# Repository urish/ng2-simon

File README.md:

# ng2-simon

A Universal Simon game written in Angular 2.

It runs on the web browser, on Arduino and also on the Raspberry PI using [angular2-iot](https://github.com/urish/angular2-iot).

➡ [Learn how to works and how you can build your own version](https://medium.com/@urish/building-simon-with-angular2-iot-fceb78bb18e5)

## Live Demo (browser)

[Go to the online version](https://urish.github.io/ng2-simon/)

## Running in a Web Browser

    npm install
    npm start

Then go to [http://localhost:3000](http://localhost:3000) in your browser.

## Running on Raspberry Pi

### Hardware Assembly

1. Connect 4 push-buttons, one button between each of pins GPIO-13, GPIO-26, GPIO-16, GPIO-21 and the ground
2. Connect 4 colored LEDs, one LED between each of pins GPIO-6, GPIO-19, GPIO-12, GPIO-20 and the ground. It is also recommended to add a 100ohm current limiting resistor in series with each LED.
3. Connect a speaker to the Raspberry PI audio jack
4. Optionally, connect a [Serial 7-Segment Display](https://www.sparkfun.com/products/11442) to the I2C pins of the Raspberry Pi: connect GPIO-2 to SDL and GPIO-3 to SCL

### Running the game

Run the following command on the Raspberry pi terminal / console:

1. Make sure you have the `sox` and `mpg123` packages installed: `sudo apt-get install sox mpg123`
2. Build the project using `npm run build:iot`
3. Run it using `sudo npm run iot`

## Running on Arduino

### Hardware Assembly

1. Connect 4 push-buttons, one button between each of Arduino pins 2, 3, 4, 5 and the ground
2. Connect 4 colored LEDs, one LED between each of Arduino pins 9, 10, 11, 12 and a current limiting resistor connected to the ground. 220ohm is a good value for the resistor.
3. Optionally, connect a small speaker between pin 8 and the ground

### Running the game

1. Connect the Arduino board to your computer
2. Upload the [StandardFirmata firmware](https://github.com/firmata/arduino) firmware to your Arduino board
3. Build the project using `npm run build:iot`
4. Run it using `npm run iot`

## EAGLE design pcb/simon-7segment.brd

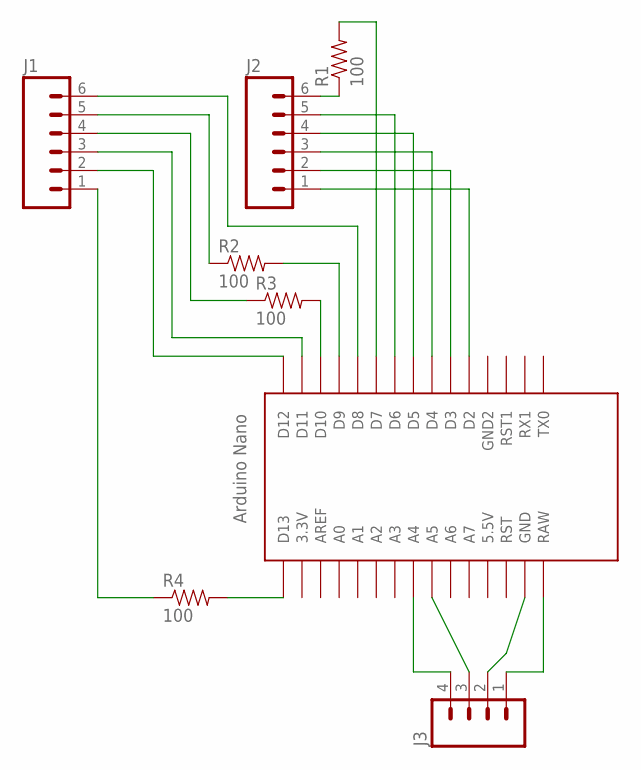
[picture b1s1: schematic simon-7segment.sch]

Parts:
J1, J2: M06SILK_FEMALE_PTH; 1X06
J3: M04LOCK_LONGPADS; 1X04_LOCK_LONGPADS
R1, R2, R3, R4: 100; AXIAL-0.4
U$1: NANO

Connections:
5V: J3.1, U$1.RAW
12: J1.1, R4.P$1 (1)
GND: J3.2, U$1.GND
unnamed: J2.1, U$1.D2
unnamed: J2.2, U$1.D3
unnamed: J2.3, U$1.D4
unnamed: J2.4, U$1.D5
unnamed: J2.5, U$1.D6
unnamed: J2.6, R1.P$1 (1)
unnamed: R1.P$2 (2), U$1.D7
unnamed: J1.6, U$1.D8
unnamed: J1.5, R2.P$1 (1)
unnamed: R2.P$2 (2), U$1.D9
unnamed: J1.4, R3.P$1 (1)
unnamed: R3.P$2 (2), U$1.D10
unnamed: J1.3, U$1.D11
unnamed: J1.2, U$1.D12
unnamed: R4.P$2 (2), U$1.D13
SCL: J3.3, U$1.A5
SDA: J3.4, U$1.A4

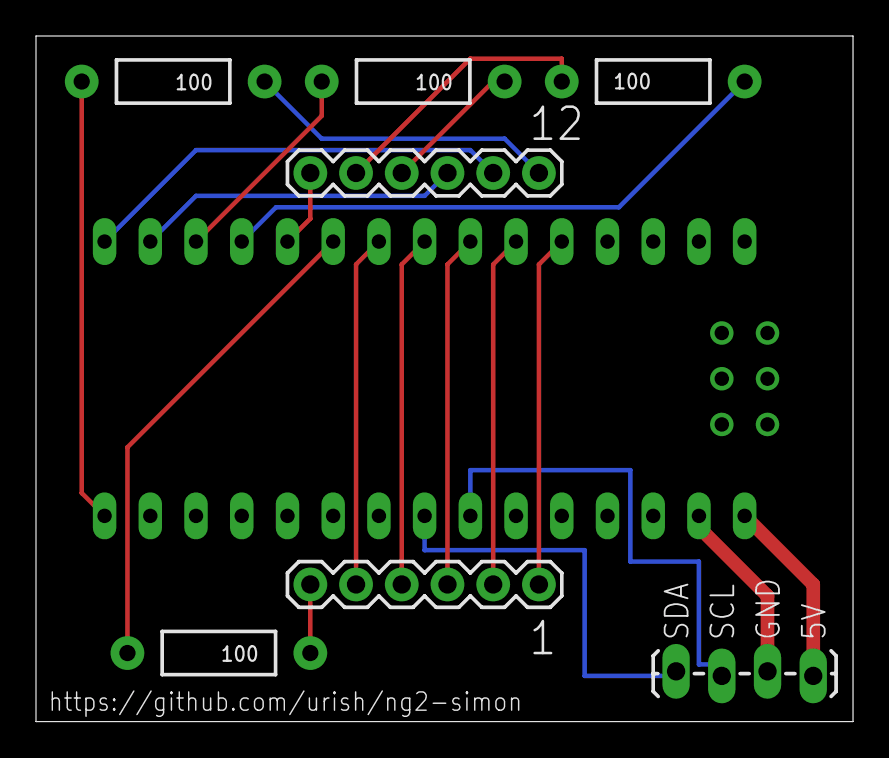
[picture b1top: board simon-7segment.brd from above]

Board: 2 copper layers, 45.4 x 38.1 mm, 8 parts (0 on the bottom side), 20 nets.

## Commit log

2016-04-18 add basic game logic
2016-04-18 chore(*): fix tslint.json
2016-04-19 feat(iot): add an entry point for IoT
2016-04-19 fix(*): fix build configration for the web version
2016-04-19 feat(game): add sound (using 8 bit audio API)
2016-04-19 fix(iot): import correct package name
2016-04-19 fix(iot): handle the case where WebAudio is not available (such as on IoT platform)
2016-04-19 feat(iot): implement AnalogSynth and SevenSegment components
2016-04-19 doc(README): update readme
2016-04-19 fix(iot): remove a debug print
2016-04-19 doc(README): add instructions for running in the browser
2016-04-19 doc(README): fix instructions
2016-04-28 doc(README): add a diagram for Arduino + instructions
2016-04-28 feat(SevenSegment): switch from cli i2c to raspi-io based i2c
2016-04-28 doc(README): update raspi instructions
2016-04-29 feat(simon): add a game over sound file
2016-04-29 feat(simon): css facelift
2016-04-29 feat(simon): deploy to gh-pages
2016-04-29 doc(README): add link to the live demo
2016-04-29 feat(simon): more pleasant level-up sound
2016-04-29 feat(simon): add a "star on github" widget
2016-04-30 fix(iot): disable johnny-five REPL
2016-05-01 fix(simon): normalize audio levels
2016-05-01 chore(*): upgrade npm deps
2016-05-01 doc(*): update project name in package.json
2016-05-01 fix(*): add raspi-io and phantomjs to optionalDependecies
    this lets us run the code on the raspberry pi
2016-05-01 feat(simon): add mp3 playing support for raspberry pi
2016-05-01 doc(README): fix a typo
2016-05-01 doc(readme): explain raspberry pi hardware setup + diagram
2016-05-01 doc(raspi): add a sample alsa config for raspberry pi
2016-05-01 feat(simon): use common base class for IoT and Web audio synth
    thanks @pascalprecht for helping out
2016-05-02 feat(simon): add raspberry pi code
    iot directives + pin mappings + seven segment display
2016-05-02 feat(simon): wait for the player before starting the game
2016-05-03 feat(iot): use raspiberry pi IO by default
2016-05-03 feat(simon): report game state and game score to firebase
2016-05-04 linear tone duration (300 -> 100)
2016-05-04 new high score sound added
2016-10-13 Initial commit (clone angular2-webpack-starter)
2016-10-13 Merge pull request #1 from tomteman/master
    linear tone duration (300 -> 100)
2016-10-13 Merge pull request #2 from tomteman/master
    new high score sound added
2016-10-13 feat(simon): keep track of the game color
    and also add some documentation
2016-10-13 core(material-design): remove extra MD dependencies
2016-10-13 refactor(simon): move to firebase bits into a service
2016-10-13 feat(simon): Use a different Firebase URL for web / iot
    fix #4
2016-10-13 feat(simon): store last button color to firebase
2016-10-13 feat(simon): add optional firebase auth
2016-10-13 feat(simon): report the current sequence index to Firebase
2016-10-13 chore(*): angular 2.0.0-rc.1
2016-10-13 add a PCB design for I2C 7Segment adapter
2016-10-13 feat(simon): indicate game over to firebase
2016-10-13 USB Audio configuration
    + explanations for asound.conf
2016-10-13 add enclouse design files (laser cut)
2016-10-13 chore(*): upgrade typings to 1.0
2016-10-13 fix(iot): add missing dependencies
    @angular/http and @angular/router-deprecated are required by angular-universal
2016-10-13 rename iot.ts -> main.iot.ts
2016-10-13 fix(iot): fix broken iot bootstrap
    Apparently, `bootstrap()` fails if the component has a `selector` property. Thus, we create an intermediate `SimonIotApp` component to bootstrap the game.
2016-10-13 add 3d model of the dowels
2016-10-13 doc(README): add a link to the blog post
2016-10-13 fix(iot): handle i2c errors gracefully
2016-10-13 Update raspberry pi pin mapping
    Apparently, some of the pins we previous used are shared with the PCM driver, thus blocking the built-in sound card from being used.
2016-10-13 refactor(*): angular 2.0 final
    also migrate to angular-cli and typescript 2
2016-10-13 cleanup(*): remove last portions of angular2-webpack-starter code
2016-10-13 refactor(*): renames files following Angular 2 style guide conventions
2016-10-15 fix(iot): add angular iot dependencies
    also fix the IoT bootstrap code
2016-10-22 feat(build): enable AoT for Web build
    also upgrade angular to 2.1
2016-10-22 fix(build): add gh-pages to pacakge.json
2016-10-22 fix(game): remove `private` from view props
    remove the `private` qualifier from properties shared with the view (for AoT)
2016-10-22 fix(iot): fix iot module configuration
2016-10-22 fix(iot): update npm dependencies
    angular 2.1.1 is not compatible with current angular-platform-node, so downgrade to 2.1.0.
    add `play-sound` and upgrade `angular2-iot` to 0.2.0
2016-10-23 chore(iot): use webpack for building iot bundle
    webpack config is based on the `universal` branch of the angular-cli
2016-10-27 feat(simon): implement automatic game timeout
    close #6
2016-11-05 fix(iot): use `CommonModule` instead of `BrowserModule`
2016-11-05 fix(iot): add SimonIotComponent
    This is the entry point of the IoT version of the game
2016-11-06 refactor(iot): remove seven-segment component
    it is now a part of angular2-iot 0.3.0
2016-11-06 chore(iot): upgrade dependencies
    use latest raspi-io, to fix deprecation warnings in node v6
2016-11-08 fix(iot): fix IoT build
    When running under IoT environment, we import the `IotModule` into `SimonModule`, in order to wire the IoT omponent.
2016-11-08 cleanup(*): remove angular-material dependency
    this reduces production bundle size from 850kb to just 490kb
2016-11-08 feat(*): add favicon
2016-11-08 fix(build): specifiy explicit version for compiler-cli
2016-11-21 feat(simon): rapidly flash LEDs at start
2017-02-19 fix the @types/jasmine devdependency from ^2.2.30 to 2.5.41

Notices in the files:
parts and their libraries:
SparkFun-Connectors: Licensing: Creative Commons ShareAlike 4.0 International - https://creativecommons.org/licenses/by-sa/4.0
